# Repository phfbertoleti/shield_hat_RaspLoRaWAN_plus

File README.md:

# Repositório - Shield/hat RaspLoRaWAN+

Este é o repositório oficial do shield/hat RaspLoRaWAN+. Este sheild/hat fornece à Raspberry Pi, com o uso de um Heltec ESP32 WiFi LoRa, os seguintes recursos:

* Envio (uplink) e recepção (downlink) de mensagens LoRaWAN (já configurado para operar com a rede da ATC no Brasil)
* Leitura de até 3 canais ADC (tensão máxima: 3V3)
* Controle de uma saída analógica (via DAC, com tensão máxima de 3V3)
* Interação com dispositivos (sensores, por exemplo) I²C, com nível de tensão de 3V3
* Escrita, linha a linha, no display OLED do Heltec ESP32 WiFi LoRa

## Funcionamento e estrutura básica dos códigos-fonte

Este shield/hat funciona com a Raspberry Pi enviando e recebendo mensagens ao Heltec ESP32 WiFi LoRa via UART (115200/8/N/1). Para tal, do lado da Raspberry Pi, é disponível um serviço chamado recebe_envia_dados_uart, totalmente escrito em C para máxima eficiência e otimização. Já do lado do Heltec ESP32 WiFi LoRa, é utilizado um software embarcado escrito na Arduino IDE, fazendo uso de FreeRTOS.

Para interagir com o serviço, é utilizado o protocolo MQTT como IPC (Inter-Processes Communication), com um broker MQTT rodando internamente na Raspberry Pi. Dessa forma, é possível interagir com todas as funcionalidades fazendo publish e subscribe em tópicos MQTT específicos.

A estrutura básica dos códigos-fonte é:

* *Pasta ESP32:* software embarcado a ser gravado no Heltec ESP32 WiFi LoRa. Antes de compilar e gravar, é preciso somente colocar as chaves LoRaWAN no arquivo LORAWAN_defs.h
* *Pasta Raspberry/recebe_envia_dados_uart:* serviço de comunicação UART entre Raspberry Pi e Heltec ESP32 WiFi LoRa, assim como IPC com MQTT
* *Pasta Raspberry/unit_files:* unit files para habilitar o serviço no systemd
* *Pasta Raspberry/Exemplos_Python:* exemplos (em Python 3.X) que exploram todos os recursos da placa
* *Pasta Hardware:* projeto completo (esquemático, layout e gerber files) de hardware do shield/hat

## Compatibilidade

Este shield/hat e seu respectivo software é compatível com todas Raspberries Pi com header de expansão de 40 pinos, como por exemplo:

* Raspberry Pi 3B
* Raspberry Pi 3B+
* Raspberry Pi Zero
* Raspberry Pi Zero W
* Raspberry Pi 4
* Raspberry Pi A+
* etc.

## Instalação dos softwares necessários na Raspberry Pi

Para instalar todos os softwares e dependências necessários na Raspberry Pi, siga o procedimento abaixo:

1. Se sua Raspberry Pi não possuir acesso à Internet, faça-a ter. 
Isso é necessário para a instalação das dependências.
2. Clone este repositório no home (/home/pi)
3. Na pasta do repositório, execute o script instala_tudo.sh como super-usuário:

```
sudo instala_tudo.sh
```

4. Aguarde a instalação automática. No fim do processo, o serviço que comunica com o shield/hat via UART e demais processos (IPC) via MQTT estará rodando. Para verificar a execução deste serviço, utilize o comando abaixo:

```
sudo systemctl status recebe_envia_esp32.service
```

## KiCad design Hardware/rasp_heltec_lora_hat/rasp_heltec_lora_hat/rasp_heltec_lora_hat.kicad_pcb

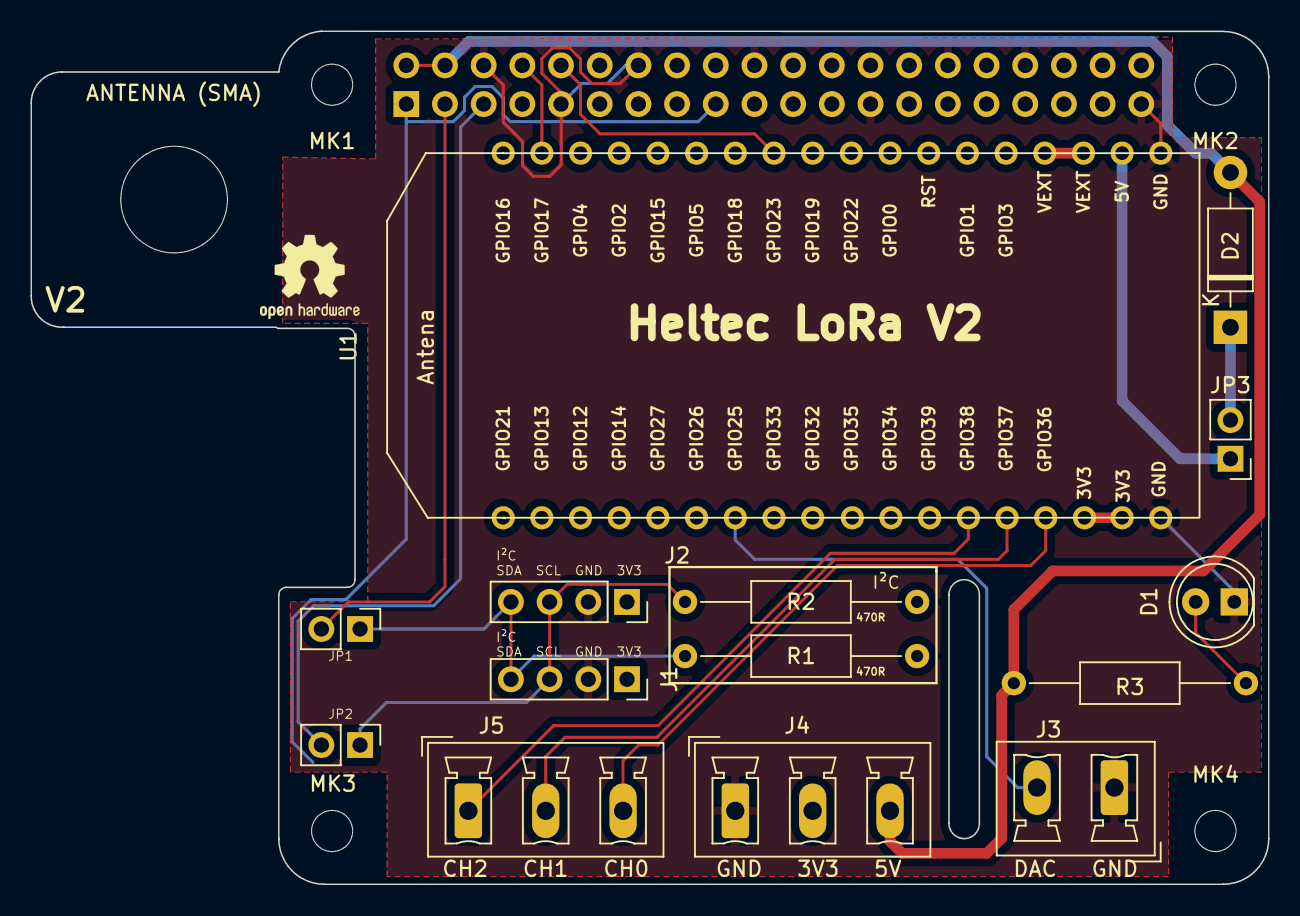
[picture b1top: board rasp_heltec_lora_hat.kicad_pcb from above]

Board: 2 copper layers, 81.3 x 56.0 mm, 20 parts (1 on the bottom side), 18 nets.

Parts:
ANTENNA (SMA): MountingHole_6mm
D1: LED_PWR_UP; LED_D5.0mm_Clear
D2: 1N5819; D_DO-41_SOD81_P10.16mm_Horizontal
J1: Conn_I2C_1; PinSocket_1x04_P2.54mm_Vertical
J2: Conn_I2C_2; PinSocket_1x04_P2.54mm_Vertical
J3: CONN_DAC2; PhoenixContact_MCV_1,5_2-G-5.08_1x02_P5.08mm_Vertical
J4: Conn_Alim; PhoenixContact_MCV_1,5_3-G-5.08_1x03_P5.08mm_Vertical
J5: Con_ADC1; PhoenixContact_MCV_1,5_3-G-5.08_1x03_P5.08mm_Vertical
JP1: JMP_I2C_SDA; PinHeader_1x02_P2.54mm_Vertical
JP2: JMP_I2C_SCL; PinHeader_1x02_P2.54mm_Vertical
JP3: JMP_ALIM_HELTEC; PinHeader_1x02_P2.54mm_Vertical
MK1, MK2, MK3, MK4: M2.5; MountingHole_2.7mm_M2.5
P1: Conn_02x20_Odd_Even; PinSocket_2x20_P2.54mm_Vertical
R1, R2, R3: 470R; R_Axial_DIN0207_L6.3mm_D2.5mm_P15.24mm_Horizontal
U1: Heltec_Wifi_LoRa_V2; Heltec_WiFi_LoRa_V2

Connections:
+3V3: J1.1, J2.1, J4.2, P1.1, P1.17, R1.1, R2.1
+5V: D2.2, J4.3, P1.2, P1.4, R3.1
/GPIO2(SDA1): JP1.2, P1.3
/GPIO3(SCL1): JP2.2, P1.5
ADC1_CH_0: J5.3, U1.33
ADC1_CH_1: J5.2, U1.32
ADC1_CH_2: J5.1, U1.31
DAC_OUTPUT: J3.2, U1.25
GND: D1.1, J1.2, J2.2, J3.1, J4.1, P1.6, P1.9, P1.14, P1.20, P1.25, P1.30, P1.34, P1.39, U1.1, U1.36
HELTEC_RX: P1.8, U1.17
HELTEC_TX: P1.10, U1.11
I2C_SCL: J1.3, J2.3, JP2.1, R2.2
I2C_SDA: J1.4, J2.4, JP1.1, R1.2
unnamed: D1.2, R3.2
unnamed: D2.1, JP3.2
unnamed: JP3.1, U1.2
unnamed: U1.34, U1.35
VEXT_HELTEC: U1.3, U1.4

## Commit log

2021-06-12 Primeiro commit
2021-06-12 Correções no README
2021-06-14 Remoção de binário
2021-09-05 Correções na escrita do OLED
2021-09-07 Atualizações de hardware:
    - Atualizada placa para uso com versão 2 do Heltec LoRa
    - Adicionado diodo 1N5819 para permitir funcionamento e programação simultaneos
    - Invertidos os conectores I2C para comportar módulos pequenos (exemplo: BMP180) conectaos diretamente na placa
2021-09-08 Adicionado software de controle do shield. Este software foi desenvolvido com QT.
2021-09-09 Atualizações:
    - Eliminada mensagem de confirmação de envio LoRaWAN (devido a conflito com topico de mensagem de downlink LoRaWAN)
    - Acrescentado local para exibir mensagens recebidas de downlink LoRaWAN no software feito em QT
